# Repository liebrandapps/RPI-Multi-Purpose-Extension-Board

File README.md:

# RPI-Multi-Purpose-Extension-Board

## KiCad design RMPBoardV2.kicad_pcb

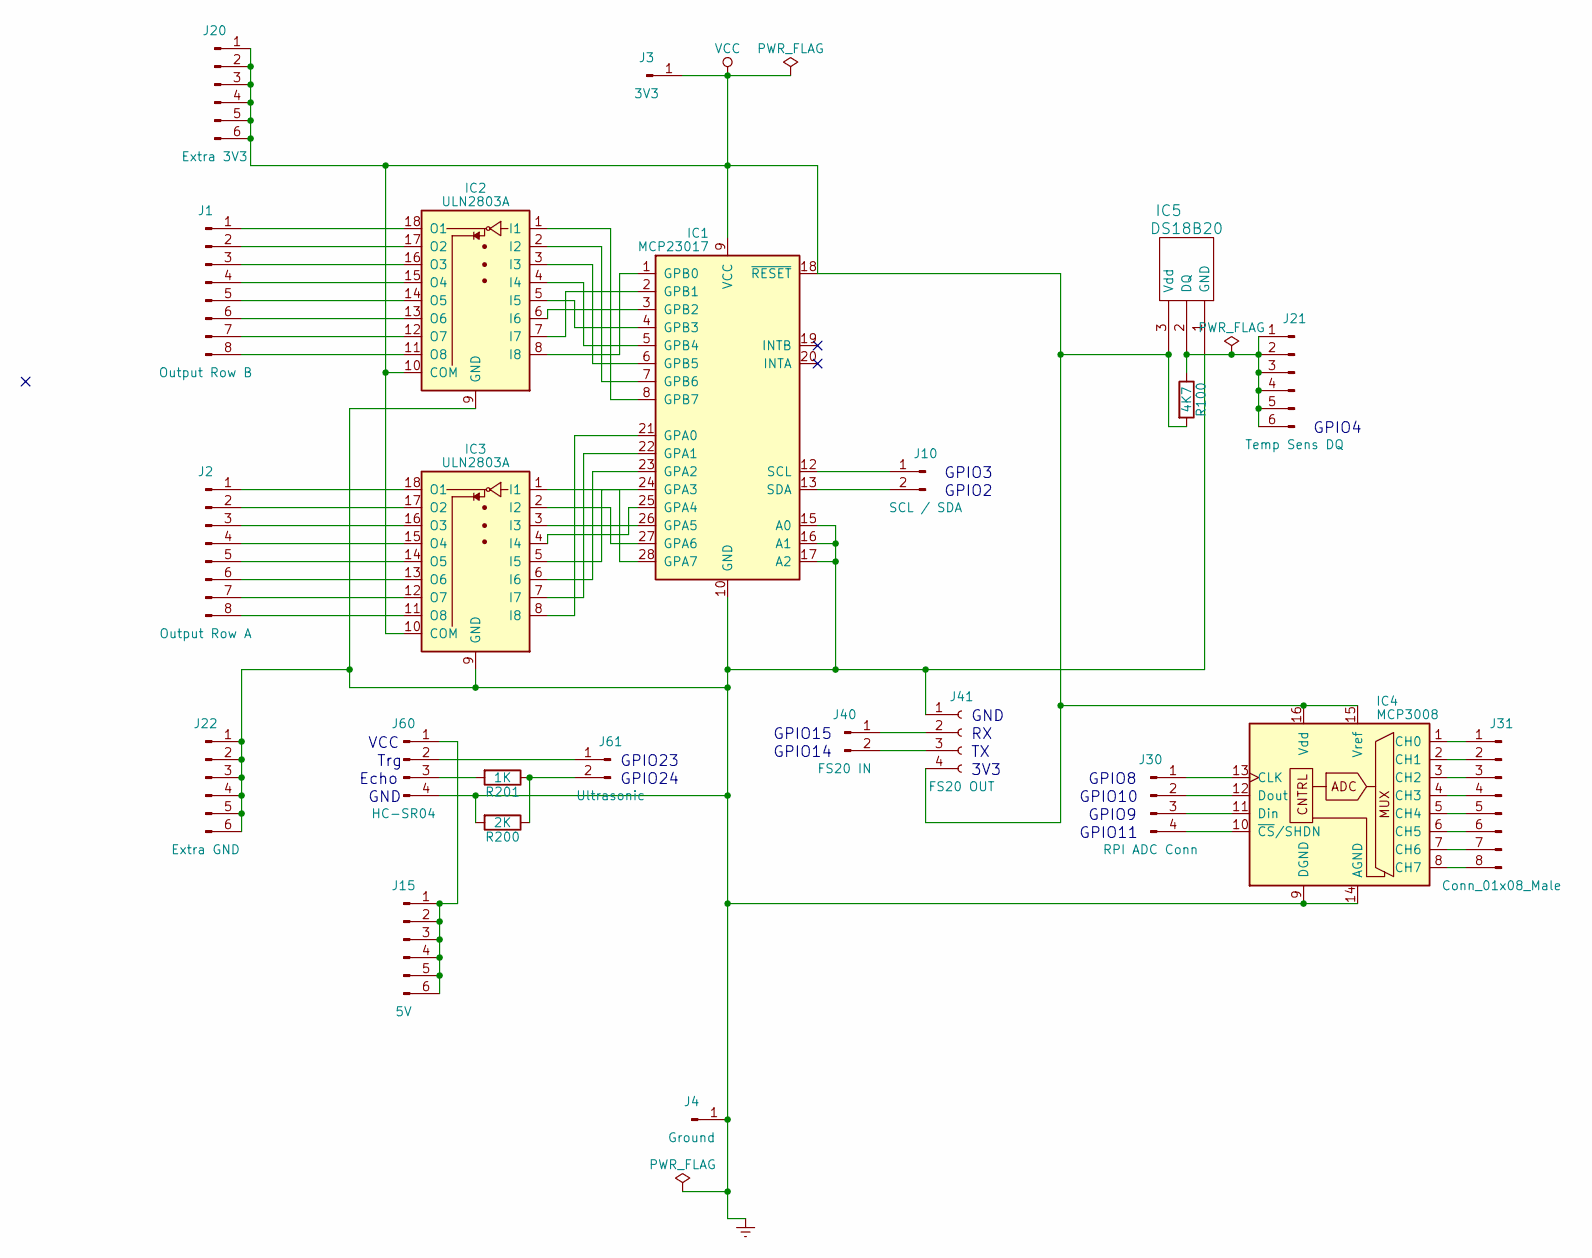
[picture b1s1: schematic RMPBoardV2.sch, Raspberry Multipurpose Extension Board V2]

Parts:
IC1: MCP23017; DIP-28_W7.62mm
IC2, IC3: ULN2803A; DIP-18_W7.62mm
IC4: MCP3008; DIP-16_W7.62mm
IC5: DS18B20; TO-92_Molded_Narrow
J1: Output Row B; Pin_Header_Straight_1x08_Pitch2.54mm
J2: Output Row A; Pin_Header_Straight_1x08_Pitch2.54mm
J3: 3V3; Pin_Header_Straight_1x01_Pitch2.54mm
J4: Ground; Pin_Header_Straight_1x01_Pitch2.54mm
J10: SCL / SDA; Pin_Header_Straight_1x02_Pitch2.54mm
J15: 5V; Pin_Header_Straight_1x06_Pitch2.54mm
J20: Extra 3V3; Pin_Header_Straight_1x06_Pitch2.54mm
J21: Temp Sens DQ; Pin_Header_Straight_1x06_Pitch2.54mm
J22: Extra GND; Pin_Header_Straight_1x06_Pitch2.54mm
J30: RPI ADC Conn; Pin_Header_Straight_1x04_Pitch2.54mm
J31: Conn_01x08_Male; Pin_Header_Straight_1x08_Pitch2.54mm
J40: FS20 IN; Pin_Header_Straight_1x02_Pitch2.54mm
J41: FS20 OUT; Socket_Strip_Straight_1x04_Pitch2.54mm
J60: HC-SR04; Pin_Header_Straight_1x04_Pitch2.54mm
J61: Ultrasonic; Pin_Header_Straight_1x02_Pitch2.54mm
R100: 4K7; R_Axial_DIN0207_L6.3mm_D2.5mm_P15.24mm_Horizontal
R200: 2K; R_Axial_DIN0207_L6.3mm_D2.5mm_P15.24mm_Horizontal
R201: 1K; R_Axial_DIN0207_L6.3mm_D2.5mm_P15.24mm_Horizontal

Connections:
Earth: IC1.10 (GND), IC1.15 (A0), IC1.16 (A1), IC1.17 (A2), IC2.9 (GND), IC3.9 (GND), IC4.9 (DGND), IC4.14 (AGND), IC5.1 (GND), J4.1, J22.1, J22.2, J22.3, J22.4, J22.5, J22.6, J41.1, J60.4, R200.2
unnamed: IC1.1 (GPB0), IC2.8 (I8)
unnamed: IC1.2 (GPB1), IC2.7 (I7)
unnamed: IC1.3 (GPB2), IC2.6 (I6)
unnamed: IC1.4 (GPB3), IC2.5 (I5)
unnamed: IC1.5 (GPB4), IC2.4 (I4)
unnamed: IC1.6 (GPB5), IC2.3 (I3)
unnamed: IC1.7 (GPB6), IC2.2 (I2)
unnamed: IC1.8 (GPB7), IC2.1 (I1)
unnamed: IC1.12 (SCL), J10.1
unnamed: IC1.13 (SDA), J10.2
unnamed: IC1.21 (GPA0), IC3.8 (I8)
unnamed: IC1.22 (GPA1), IC3.7 (I7)
unnamed: IC1.23 (GPA2), IC3.6 (I6)
unnamed: IC1.24 (GPA3), IC3.5 (I5)
unnamed: IC1.25 (GPA4), IC3.4 (I4)
unnamed: IC1.26 (GPA5), IC3.3 (I3)
unnamed: IC1.27 (GPA6), IC3.2 (I2)
unnamed: IC1.28 (GPA7), IC3.1 (I1)
unnamed: IC2.11 (O8), J1.8
unnamed: IC2.12 (O7), J1.7
unnamed: IC2.13 (O6), J1.6
unnamed: IC2.14 (O5), J1.5
unnamed: IC2.15 (O4), J1.4
unnamed: IC2.16 (O3), J1.3
unnamed: IC2.17 (O2), J1.2
unnamed: IC2.18 (O1), J1.1
unnamed: IC3.11 (O8), J2.8
unnamed: IC3.12 (O7), J2.7
unnamed: IC3.13 (O6), J2.6
unnamed: IC3.14 (O5), J2.5
unnamed: IC3.15 (O4), J2.4
unnamed: IC3.16 (O3), J2.3
unnamed: IC3.17 (O2), J2.2
unnamed: IC3.18 (O1), J2.1
unnamed: IC4.1 (CH0), J31.1
unnamed: IC4.2 (CH1), J31.2
unnamed: IC4.3 (CH2), J31.3
unnamed: IC4.4 (CH3), J31.4
unnamed: IC4.5 (CH4), J31.5
unnamed: IC4.6 (CH5), J31.6
unnamed: IC4.7 (CH6), J31.7
unnamed: IC4.8 (CH7), J31.8
unnamed: IC4.10 (~CS~/SHDN), J30.4
unnamed: IC4.11 (Din), J30.3
unnamed: IC4.12 (Dout), J30.2
unnamed: IC4.13 (CLK), J30.1
unnamed: IC5.2 (DQ), J21.1, J21.2, J21.3, J21.4, J21.5, J21.6, R100.1
unnamed: J15.1, J15.2, J15.3, J15.4, J15.5, J15.6, J60.1
unnamed: J40.1, J41.2
unnamed: J40.2, J41.3
unnamed: J60.2, J61.1
unnamed: J60.3, R201.2
unnamed: J61.2, R200.1, R201.1
VCC: IC1.9 (VCC), IC1.18 (~RESET), IC2.10 (COM), IC3.10 (COM), IC4.15 (Vref), IC4.16 (Vdd), IC5.3 (Vdd), J3.1, J20.1, J20.2, J20.3, J20.4, J20.5, J20.6, J41.4, R100.2

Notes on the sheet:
Echo
Trg
VCC
GND
GPIO24
GPIO23
3V3
GPIO15
GPIO14
GPIO3
GPIO2
GPIO4
GPIO8
GPIO10
GPIO9
GPIO11

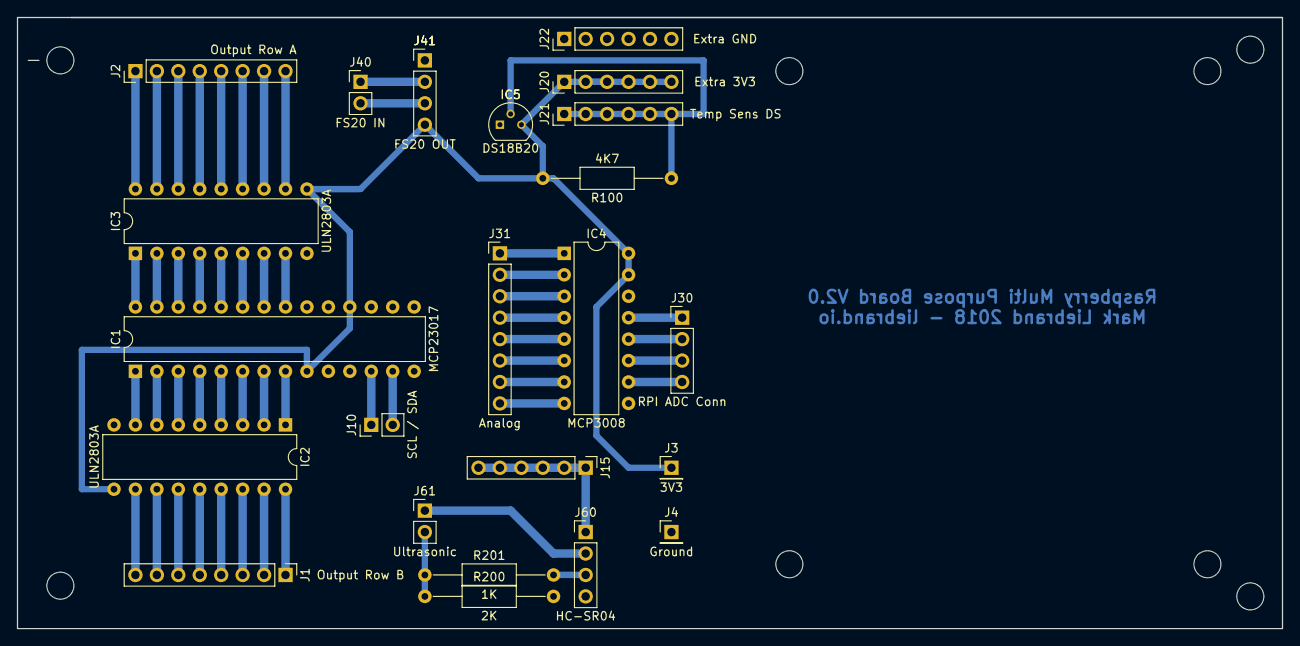
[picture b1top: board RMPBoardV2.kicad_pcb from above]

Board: 2 copper layers, 149.9 x 72.4 mm, 23 parts (0 on the bottom side), 55 nets.
